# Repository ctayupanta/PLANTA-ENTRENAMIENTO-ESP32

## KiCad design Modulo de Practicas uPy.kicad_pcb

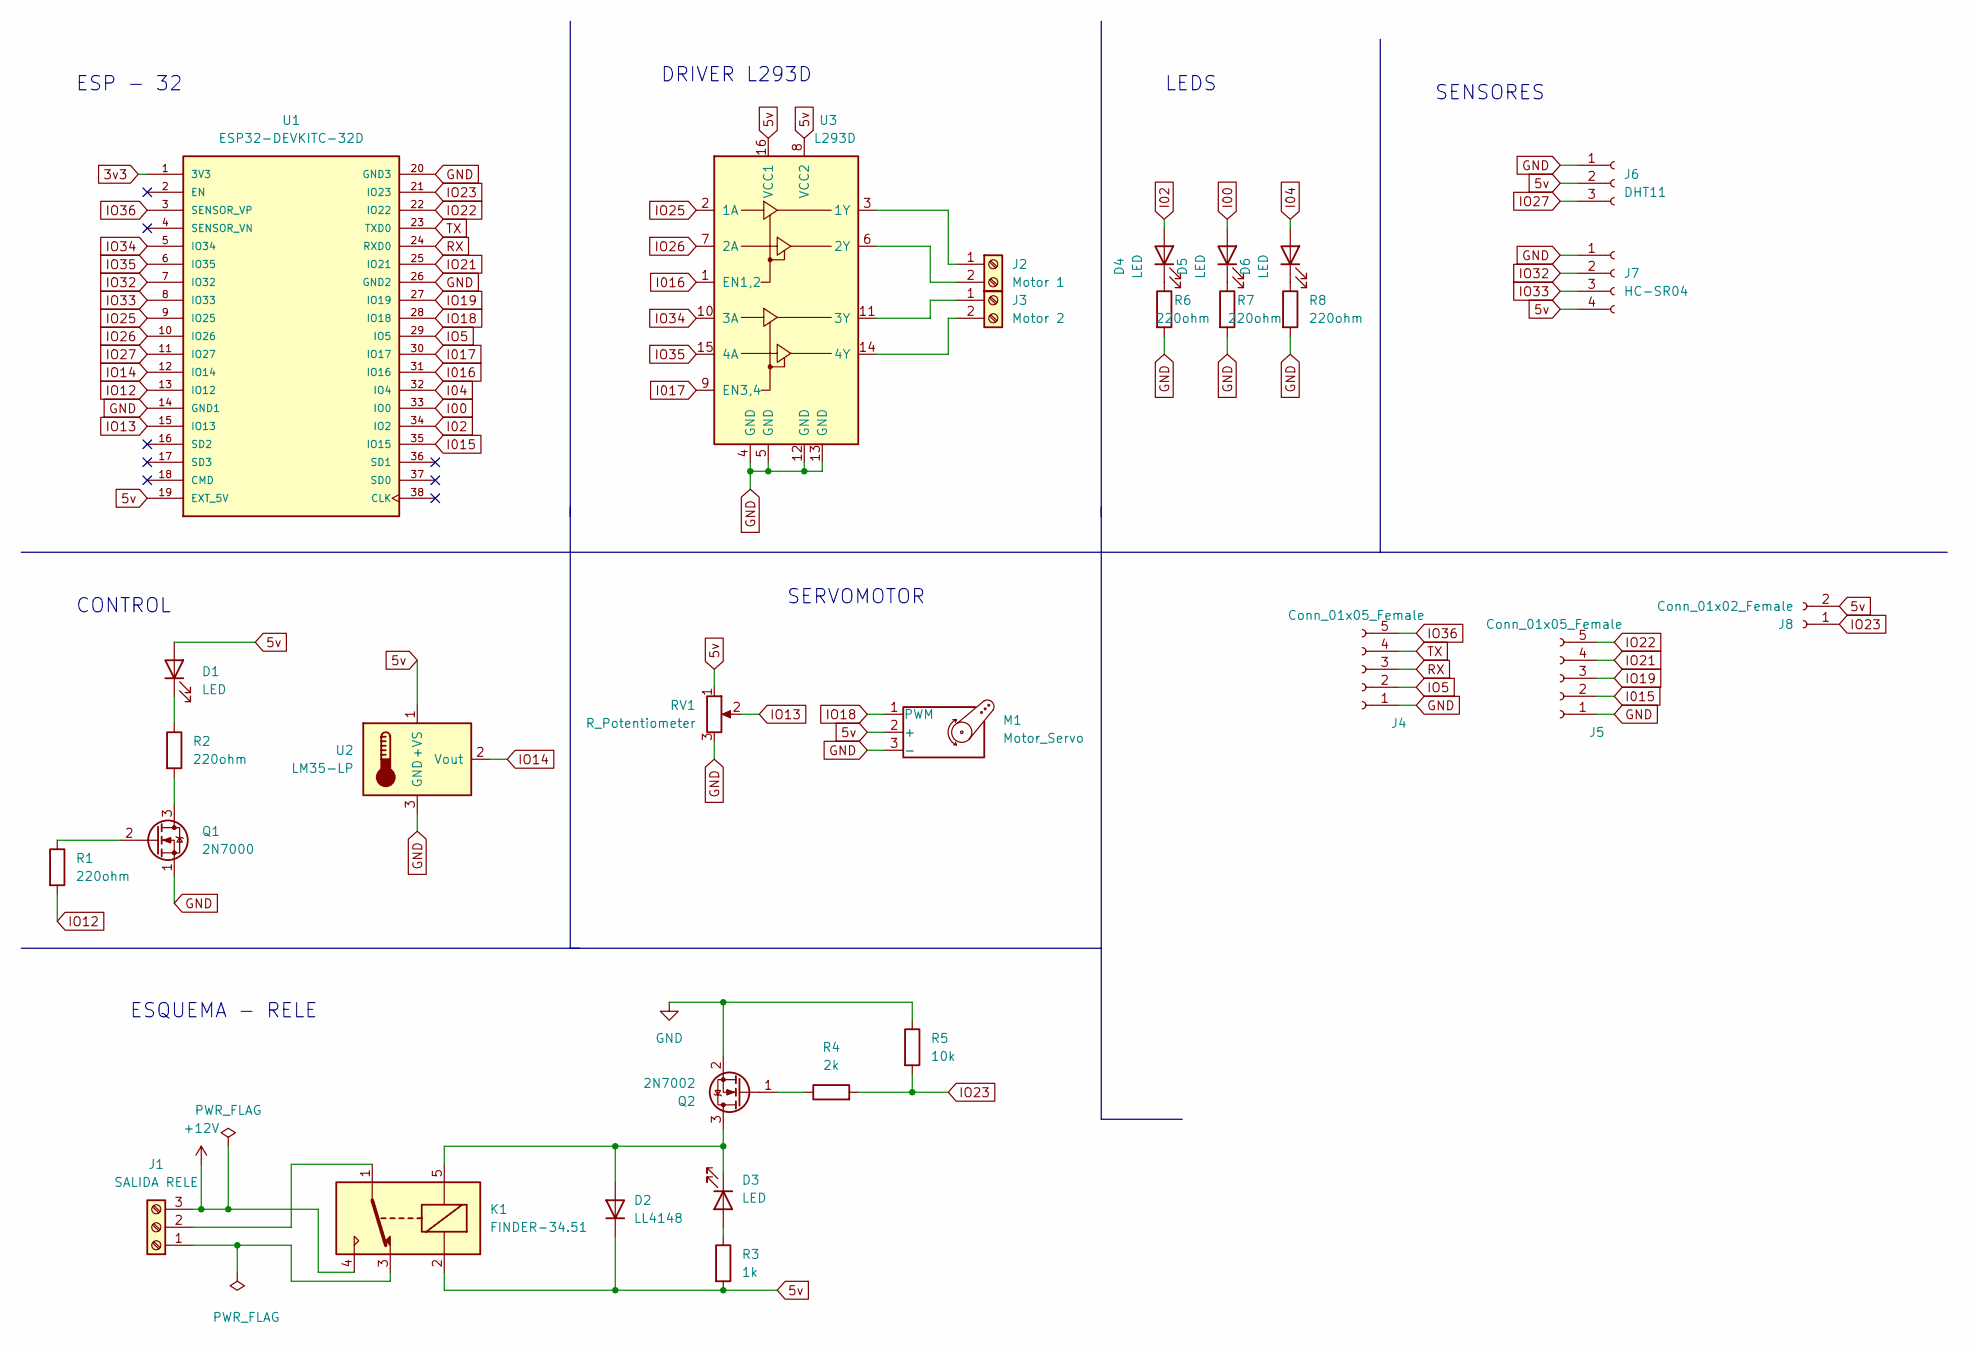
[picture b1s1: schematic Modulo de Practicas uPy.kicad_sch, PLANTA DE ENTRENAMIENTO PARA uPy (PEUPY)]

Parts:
D1: LED; LED_1W_3W_R8
D2: LL4148; D_0805_2012Metric
D3, D4, D5, D6: LED; LED_0805_2012Metric
J1: SALIDA RELE; TerminalBlock_bornier-3_P5.08mm
J2: Motor 1; TerminalBlock_bornier-2_P5.08mm
J3: Motor 2; TerminalBlock_bornier-2_P5.08mm
J4, J5: Conn_01x05_Female; PinSocket_1x05_P2.54mm_Vertical
J6: DHT11; PinHeader_1x03_P2.54mm_Vertical
J7: HC-SR04; PinHeader_1x04_P2.54mm_Vertical
J8: Conn_01x02_Female; PinHeader_1x02_P2.54mm_Vertical
K1: FINDER-34.51; Relay_SPDT_SANYOU_SRD_Series_Form_C
M1: Motor_Servo; PinHeader_1x03_P2.54mm_Vertical
Q1: 2N7000; TO-92_Inline
Q2: 2N7002
R1, R6, R7, R8: 220ohm; R_0805_2012Metric
R2: 220ohm; R_Axial_DIN0204_L3.6mm_D1.6mm_P7.62mm_Horizontal
R3: 1k; R_0805_2012Metric
R4: 2k; R_0805_2012Metric
R5: 10k; R_0805_2012Metric
RV1: R_Potentiometer; TRIM_COM-09806
U1: ESP32-DEVKITC-32D; MODULE_ESP32-DEVKITC-32D; PARTREV 4
U2: LM35-LP; PinHeader_1x03_P2.54mm_Vertical
U3: L293D; DIP-16_W7.62mm

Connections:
3v3: U1.1 (3V3)
5v: D1.2 (A), D2.1 (K), J6.2, J7.4, J8.2, K1.2, M1.2 (+), R3.2, RV1.1, U1.19 (EXT_5V), U2.1 (+VS), U3.8 (VCC2), U3.16 (VCC1); also elsewhere on the board
+12V: J1.3, K1.4
GND: J4.1, J5.1, J6.1, J7.1, M1.3 (-), Q1.1 (S), Q2.2 (S), R5.1, R6.2, R7.2, R8.2, RV1.3, U1.14 (GND1), U1.20 (GND3), U1.26 (GND2), U2.3 (GND), U3.4 (GND), U3.5 (GND), U3.12 (GND), U3.13 (GND); also elsewhere on the board
I00: D5.2 (A), U1.33 (IO0)
I02: D4.2 (A), U1.34 (IO2)
I04: D6.2 (A), U1.32 (IO4)
I015: J5.2, U1.35 (IO15)
I016: U1.31 (IO16), U3.1 (EN1,2)
I017: U1.30 (IO17), U3.9 (EN3,4)
IO5: J4.2, U1.29 (IO5)
IO12: R1.2, U1.13 (IO12)
IO13: RV1.2, U1.15 (IO13)
IO14: U1.12 (IO14), U2.2 (Vout)
IO18: M1.1 (PWM), U1.28 (IO18); also elsewhere on the board
IO19: J5.3, U1.27 (IO19)
IO21: J5.4, U1.25 (IO21)
IO22: J5.5, U1.22 (IO22)
IO23: J8.1, R4.2, R5.2, U1.21 (IO23)
IO25: U1.9 (IO25), U3.2 (1A)
IO26: U1.10 (IO26), U3.7 (2A)
IO27: J6.3, U1.11 (IO27)
IO32: J7.2, U1.7 (IO32)
IO33: J7.3, U1.8 (IO33)
IO34: U1.5 (IO34), U3.10 (3A)
IO35: U1.6 (IO35), U3.15 (4A)
IO36: J4.5, U1.3 (SENSOR_VP)
unnamed: D1.1 (K), R2.1
unnamed: D2.2 (A), D3.1 (K), K1.5, Q2.3 (D)
unnamed: D3.2 (A), R3.1
unnamed: D4.1 (K), R6.1
unnamed: D5.1 (K), R7.1
unnamed: D6.1 (K), R8.1
unnamed: J1.1, K1.3
unnamed: J1.2, K1.1
unnamed: J2.1, U3.3 (1Y)
unnamed: J2.2, U3.6 (2Y)
unnamed: J3.1, U3.11 (3Y)
unnamed: J3.2, U3.14 (4Y)
unnamed: Q1.2 (G), R1.1
unnamed: Q1.3 (D), R2.2
unnamed: Q2.1 (G), R4.1
RX: J4.3, U1.24 (RXD0)
TX: J4.4, U1.23 (TXD0)

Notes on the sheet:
SERVOMOTOR
LEDS
ESQUEMA - RELE
CONTROL
SENSORES
ESP - 32
DRIVER L293D

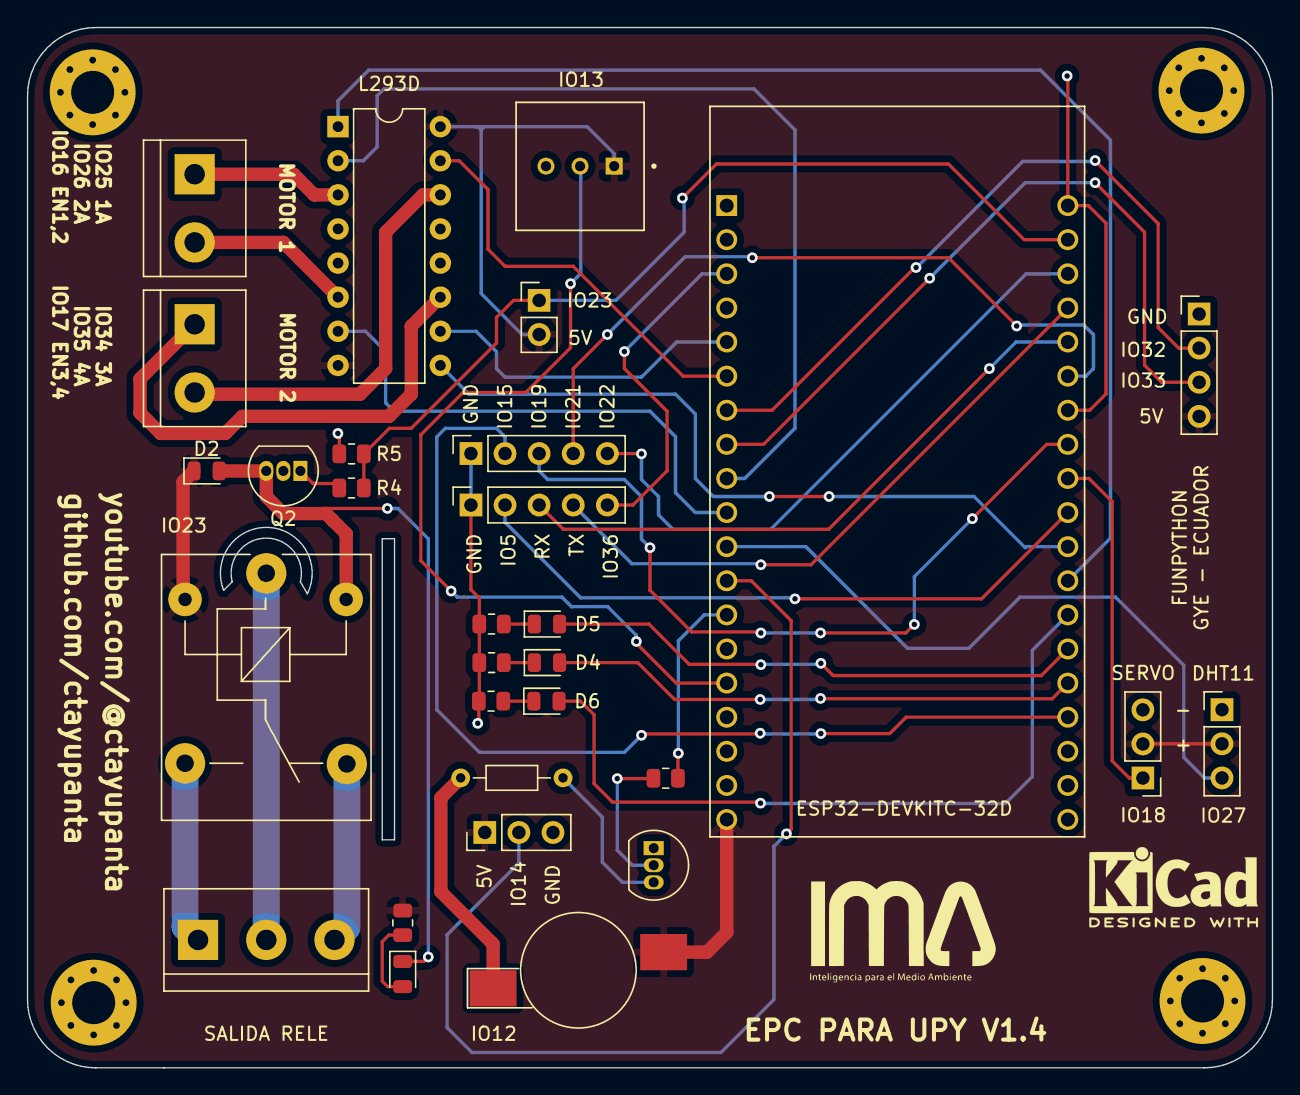
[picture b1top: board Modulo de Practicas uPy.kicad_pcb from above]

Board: 2 copper layers, 92.7 x 77.5 mm, 30 parts (0 on the bottom side), 43 nets.

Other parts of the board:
IO18: Motor_Servo; PinHeader_1x03_P2.54mm_Vertical

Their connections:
5v: IO18.2 (+); also elsewhere on the board
GND: IO18.3 (-); also elsewhere on the board
IO18: IO18.1 (PWM); also elsewhere on the board

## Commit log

2023-05-26 segunda version
2023-05-26 add foto
2023-05-26 add comentario foto
2023-05-26 add comentario foto 2
2023-05-26 add comentario foto 3
2023-05-30 Actualización de version 1.4
